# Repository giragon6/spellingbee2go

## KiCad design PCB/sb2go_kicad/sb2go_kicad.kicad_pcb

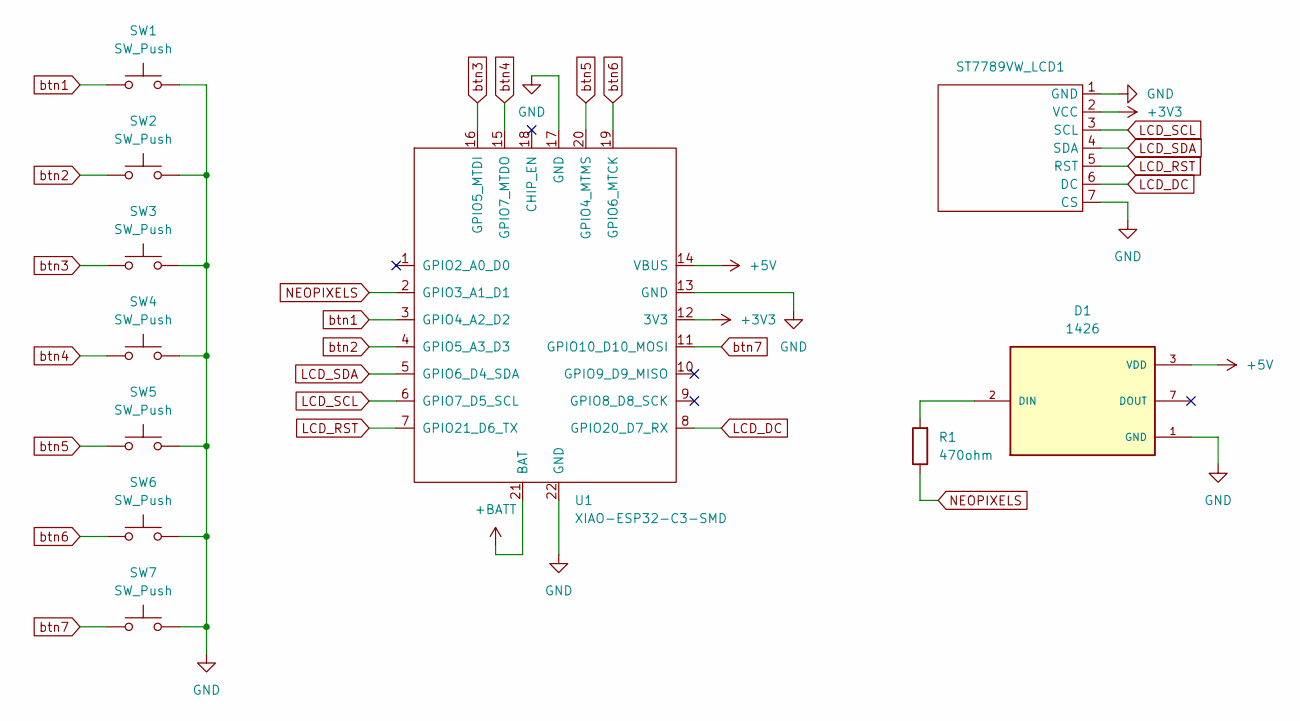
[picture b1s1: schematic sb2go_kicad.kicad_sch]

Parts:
D1: 1426; LED_1426; PARTREV v2
R1: 470ohm; R_Axial_DIN0207_L6.3mm_D2.5mm_P7.62mm_Horizontal
ST7789VW_LCD1: ST7789V_or_something
SW1, SW2, SW3, SW4, SW5, SW6, SW7: SW_Push; SW_Cherry_MX_1.00u_PCB
U1: XIAO-ESP32-C3-SMD

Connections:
+3V3: ST7789VW_LCD1.2 (VCC), U1.12 (3V3)
+5V: D1.3 (VDD), D1.6 (VDD), U1.14 (VBUS)
+BATT: U1.21 (BAT)
GND: D1.1 (GND), D1.4 (GND), D1.5 (GND), D1.8 (GND), ST7789VW_LCD1.1 (GND), ST7789VW_LCD1.7 (CS), SW1.2, SW2.2, SW3.2, SW4.2, SW5.2, SW6.2, SW7.2, U1.13 (GND), U1.17 (GND), U1.22 (GND)
LCD_DC: ST7789VW_LCD1.6 (DC), U1.8 (GPIO20_D7_RX)
LCD_RST: ST7789VW_LCD1.5 (RST), U1.7 (GPIO21_D6_TX)
LCD_SCL: ST7789VW_LCD1.3 (SCL), U1.6 (GPIO7_D5_SCL)
LCD_SDA: ST7789VW_LCD1.4 (SDA), U1.5 (GPIO6_D4_SDA)
NEOPIXELS: R1.1, U1.2 (GPIO3_A1_D1)
unnamed: D1.2 (DIN), R1.2
btn1: SW1.1, U1.3 (GPIO4_A2_D2)
btn2: SW2.1, U1.4 (GPIO5_A3_D3)
btn3: SW3.1, U1.16 (GPIO5_MTDI)
btn4: SW4.1, U1.15 (GPIO7_MTDO)
btn5: SW5.1, U1.20 (GPIO4_MTMS)
btn6: SW6.1, U1.19 (GPIO6_MTCK)
btn7: SW7.1, U1.11 (GPIO10_D10_MOSI)

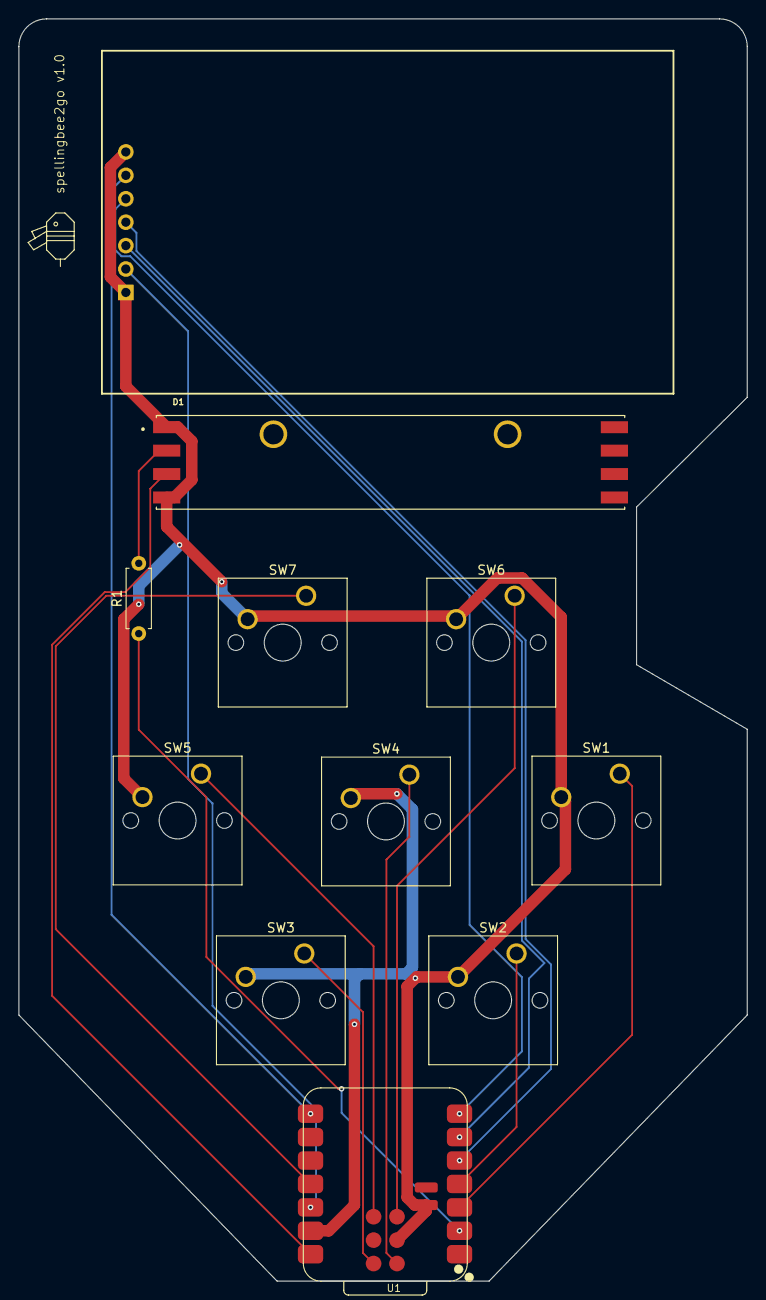
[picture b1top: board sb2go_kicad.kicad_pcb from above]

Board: 2 copper layers, 79.0 x 136.9 mm, 11 parts (0 on the bottom side), 16 nets.

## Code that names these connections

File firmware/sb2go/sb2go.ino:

#define IS_SIM

#include "words.h"
#include <Adafruit_NeoPixel.h>
#ifdef IS_SIM
    #include <Adafruit_GFX.h>
    #include "Adafruit_ILI9341.h"
#else
    #include <Arduino_GFX_Library.h>
#endif

// hardware mappings
// ----------------------------------
// neopixels       <--   2
// button numbers  <--   button pins
//  7 6                   11 19
// 5 4 1           <--   20 15 3
//  3 2                   16 4
// screen sda      <--   5
// screen scl      <--   6
// screen rst      <--   7
// screen dc       <--   8

// sim mappings
// ----------------------------------
// neopixels       <--   2
// button numbers  <--   button pins
//  7 6                   11 19
// 5 4 1           <--   20 15 3
//  3 2                   16 4
// screen sda      <--   5
// screen scl      <--   6
// screen rst      <--   7
// screen dc       <--   8

#define NUM_NEOPIXELS 8
#define NUM_BTNS 7
#ifdef IS_SIM
    #define SCREEN_WIDTH 128
    #define SCREEN_HEIGHT 64

    #define PIN_NEOPIXELS D9
    #define PIN_BTN_1 D2
    #define PIN_BTN_2 D3
    #define PIN_BTN_3 D6
    #define PIN_BTN_4 D4
    #define PIN_BTN_5 D5
    #define PIN_BTN_6 D1
    #define PIN_BTN_7 D0
    #define PIN_LCD_DC D7

    Adafruit_ILI9341 screen = Adafruit_ILI9341(-1, D7);
#else
    #define SCREEN_WIDTH 320
    #define SCREEN_HEIGHT 240

    #define PIN_NEOPIXELS 2
    #define PIN_BTN_1 3
    #define PIN_BTN_2 4
    #define PIN_BTN_3 16
    #define PIN_BTN_4 15
    #define PIN_BTN_5 20
    #define PIN_BTN_6 19
    #define PIN_BTN_7 11
    #define PIN_LCD_SDA 5
    #define PIN_LCD_SCL 6
    #define PIN_LCD_RST 7
    #define PIN_LCD_DC 8

    Arduino_DataBus *bus = new Arduino_HWSPI(PIN_LCD_DC /* DC */, GFX_NOT_DEFINED /* CS */);
    Arduino_GFX *gfx = new Arduino_ST7789(bus, PIN_LCD_RST /* RST */, 0 /* rotation */);
#endif

Adafruit_NeoPixel NeoPixel(NUM_NEOPIXELS, PIN_NEOPIXELS, NEO_GRB + NEO_KHZ800);
const u_int8_t BTN_PINS[7] = { 
    PIN_BTN_1, PIN_BTN_2, PIN_BTN_3, 
    PIN_BTN_4, PIN_BTN_5, PIN_BTN_6, 
    PIN_BTN_7 
};
bool btnLast[7] = { LOW, LOW, LOW, LOW, LOW, LOW, LOW };

void handleBtnPress(int btnId) {

}

void setup() {
    #ifdef IS_SIM
        screen.begin();

        screen.setCursor(10, 10);
        screen.setTextColor(ILI9341_RED);
        screen.setTextSize(3);
        screen.println("Hello, screen!");
    #else
        gfx->begin();

        gfx->fillScreen(RGB565_BLACK);
        gfx->setCursor(10, 10);
        gfx->setTextColor(RGB565_RED);
        gfx->println("Hello, screen!");
    #endif

    NeoPixel.begin();

    // test neopixels by turning green
    NeoPixel.clear();
    for (int pixel = 0; pixel < 8; pixel++) {           
        NeoPixel.setPixelColor(pixel, NeoPixel.Color(0, 255, 0));  
        NeoPixel.show();                                           
    }

    for (u_int8_t i = 0; i < NUM_BTNS; i++) {
        pinMode(BTN_PINS[i], INPUT_PULLUP);
    }
}

void loop() {
    for (u_int8_t i = 0; i < NUM_BTNS; i++) {
        bool btnStatus = digitalRead(BTN_PINS[i]);
        if (btnStatus == HIGH && btnLast[i] == LOW) {
            handleBtnPress(i);
        }
        btnLast[i] = btnStatus;
    }
}

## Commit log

2026-06-08 init
2026-06-08 add word list
2026-06-17 add words as header file
2026-06-17 gitignore
2026-06-17 add kicad files
2026-06-17 add janky wokwi sim diagram
2026-06-19 screen test code
